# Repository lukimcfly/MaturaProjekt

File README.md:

# Maturaprojekt — Analoger Synthesizer

Physisches Produkt: analoger Synthesizer mit 3 Oszillatoren, Mixer, Amplifier
und Distortion. Dazu eine Fourier-Analyse von analogem und digitalem Ton sowie
die schriftlichen Abgabedokumente.

**Abgabetermin: 10. November 2026**
**Zwischenziel: physisches Produkt fertig bis zu den Herbstferien**

## Stand (22.09.2026)

**Alles bestellbereit.** Schaltplan, drei Platinen und Einkauf sind fertig; die
Warenkörbe bei Tayda, LCSC und Conrad sind gefüllt, JLCPCB braucht noch den Login.

| | |
|---|---|
| Gesamtschaltplan | ERC-sauber: 0 Fehler, 0 Warnungen |
| Oszillator-Platine (**3×** pro Gerät) | DRC-sauber, 0 offene Netze |
| Filter-Platine (**4×** pro Gerät) | DRC-sauber, 0 offene Netze |
| Hauptplatine (1×) | DRC-sauber, 0 offene Netze |
| Fertigungsdaten | vollständig in [`Platinen/Fertigung/`](Platinen/Fertigung/), inkl. Bestückung der SMD-Chips |
| Einkauf für 2 Geräte | **rund CHF 378** inkl. Platinen, Versand und MWST – [`Einkauf/BESTELLEN.md`](Einkauf/BESTELLEN.md) |

Nächster Schritt: bestellen, möglichst bis 24.09. (danach chinesische Feiertage).
Was sich am 22.09. geändert hat, steht im [Tagebuch vom 22.09.](diary/2026-09-22.md).

## Ordnerstruktur

| Ordner | Inhalt |
|---|---|
| [`diary/`](diary/README.md) | Arbeitstagebuch, eine Datei pro Arbeitstag |
| [`plan/`](plan/zeitplan-bis-herbstferien.md) | Zeitpläne |
| [`quellen/`](quellen/lernmaterial.md) | Lernmaterial, später Quellenverzeichnis |
| [`Bilder/`](Bilder/README.md) | Schaltpläne, Aufbaufotos, Messungen |
| [`Schul-Unterlagen/`](Schul-Unterlagen/README.md) | Vorgaben, Kriterien, Formulare von der Schule |
| [`Unsere-Materialien/`](Unsere-Materialien/README.md) | Logbuch und schriftlicher Kommentar zur Abgabe |
| [`SynthesizerFinal/`](SynthesizerFinal/README.md) | Gesamtschaltplan des Synthesizers (KiCad) |
| [`Platinen/`](Platinen/README.md) | Die drei Leiterplatten: Layout, Gerber, Stücklisten, Verdrahtung |
| [`Einkauf/`](Einkauf/BESTELLEN.md) | Einkaufsliste (Excel), Bestellanleitung, Sicherungskopien der Warenkörbe |
| [`Werkzeuge/`](Werkzeuge/README.md) | Die Skripte, mit denen Schaltplan und Platinen erzeugt wurden |
| `KicadCircuit/` | Ursprüngliche Einzelschaltpläne (Vorstufe, nur noch als Vergleich) |

## Arbeitsregel

Der Arbeitsprozess wird **immer direkt nach dem Arbeiten** dokumentiert.

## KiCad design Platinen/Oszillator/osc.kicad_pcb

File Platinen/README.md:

# Leiterplatten

Aus dem Gesamtschaltplan ([`../SynthesizerFinal/`](../SynthesizerFinal/README.md))
sind **drei** Leiterplatten abgeleitet. Nicht neun: die drei Oszillatoren sind
elektrisch identisch, die vier Filter ebenfalls — es gibt also drei Layouts, von
denen zwei mehrfach bestückt werden.

| Platine | Ordner | Stück | Grösse | Bauteile | Stand |
|---|---|---|---|---|---|
| Oszillator | [`Oszillator/`](Oszillator/) | **3×** | 108,1 × 108,1 mm | 57 | fertig geroutet, DRC sauber |
| Filter | [`Filter/`](Filter/) | **4×** | 80,1 × 68,1 mm | 22 | fertig geroutet, DRC sauber |
| Hauptplatine | [`Hauptplatine/`](Hauptplatine/) | 1× | 96,1 × 98,1 mm | 46 | fertig geroutet, DRC sauber |

Bei allen drei Platinen gilt: **kein DRC-Fehler, kein offenes Netz, Massefläche in
einem zusammenhängenden Stück.** Die Fertigungsdaten in `Fertigung/` sind
vollständig und gehören zu genau diesem Stand.

Filter und Hauptplatine bleiben unter **100 × 100 mm**. Das ist keine
willkürliche Grenze: die meisten günstigen Platinenhersteller haben genau dort
ihre Preisstufe.

Die **Oszillator-Platine ist grösser** — 108,1 × 108,1 mm. Sie trägt 57 Bauteile,
wo die Hauptplatine 46 auf ähnlicher Fläche trägt, und wurde vergrössert, weil
sich zwei Netze partout nicht routen liessen und Platzmangel als Ursache vermutet
wurde.

> **Diese Vermutung war falsch.** Die beiden Netze scheiterten an zwei *selbst
> gesetzten* Sperrflächen, nicht an der Fläche (siehe unten). Ob die Platine
> deshalb auch wieder unter 100 × 100 mm passt, ist **noch nicht nachgeprüft** —
> das steht als offener Punkt im [Tagebuch](../diary/2026-09-16.md). Solange das
> offen ist, gilt die 108-mm-Version: sie ist vollständig geroutet und geprüft.

> **Beim Bestellen beachten:** Mit 108 mm fällt diese eine Platine aus der
> 100-×-100-mm-Preisstufe, und sie wird **dreimal** gebraucht. Wer Geld sparen
> will, prüft vorher den offenen Punkt oben.

## Was wo liegt

| Ordner / Datei | Inhalt |
|---|---|
| `Oszillator/`, `Filter/`, `Hauptplatine/` | je ein vollständiges KiCad-Projekt (`.kicad_pro`, `.kicad_sch`, `.kicad_pcb`). Zum Ansehen das `.kicad_pro` öffnen |
| `Fertigung/*.zip` | die Dateien für den Platinenhersteller: Gerber, Bohrdaten, Bohrplan. So hochladen wie sie sind |
| `Stuecklisten/` | eine Stückliste pro Platine |
| [`VERDRAHTUNG.md`](VERDRAHTUNG.md) | **die wichtigste Datei beim Zusammenbau**: welches Kabel von wo nach wo, Draht für Draht |
| [`BEDIENFELD-ERGAENZUNGEN.md`](BEDIENFELD-ERGAENZUNGEN.md) | nachträglich dazugekommen: Oszillator ein/aus, Mixer-Fader, Lautsprecherklemmen statt eingebautem Lautsprecher, Modus-Taster, Arduino-Anschluss |
| `*-bestueckung.pdf` | Bestückungsplan zum Ausdrucken |

## Aufbau der Platinen

Zweilagig, Signale auf der Oberseite, **die ganze Unterseite ist Massefläche**.
Das ist bei Audio die entscheidende Entscheidung: der Rückstrom findet immer den
kürzesten Weg direkt unter seiner Leiterbahn, statt einen Umweg zu suchen und
dabei Störungen einzusammeln.

Leiterbahnen: 0,3 mm für Signale, 0,6 mm für die Versorgung.

### Eine bewusste Ausnahme auf der Oszillator-Platine

Beim Routen galt zusätzlich die selbst gesetzte Regel: **keine Leiterbahn auf der
Rückseite unter einem IC**. Ein Schlitz in der Massefläche zwingt den Rückstrom
zu einem Umweg, und ausgerechnet unter einem IC ist das am unangenehmsten.

Für **ein** Netz — `O1_AINV`, den Summierknoten von `U103` — ist diese Regel
aufgehoben. Ohne sie kam das Netz nicht durch, und zwar nachweislich: mit
Sperrfläche scheitert die Wegsuche auch nach **444 Sekunden**.

Was das kostet, ist nachgemessen und nicht geschätzt:

| | |
|---|---|
| Verlust an Massefläche | **73 mm² von 10 517 mm² = 0,69 %** |
| Massefläche danach | **ein** zusammenhängendes Stück, keine Inseln |
| Betroffenes IC | `U103` — **das IC, zu dem das Netz selbst führt** |

Der Schlitz liegt also unter dem Baustein, an dessen Pin die Leitung ohnehin
ankommt, nicht quer unter einem unbeteiligten IC. Und bei Audiofrequenzen
(≤ 20 kHz) fliesst der Rückstrom ohnehin breit verteilt; eng an der Leiterbahn
klebt er erst weit oberhalb von 1 MHz. Für eine Digitalplatine wäre das ein
Fehler, hier ist es vertretbar.

> Wer dieses Layout später überarbeitet: **den Schlitz nicht „aufräumen"**, ohne
> das Netz neu zu routen — sonst ist die Platine wieder unvollständig.

## Die Bedienelemente sitzen **nicht** auf den Platinen

Potis, Schalter und Buchsen kommen ins Bedienfeld und werden mit Kabeln an die
Platinen gesteckt (JST-XH, 2,5 mm). Das sind 153 Drähte, einer pro Lötfahne.
Alle stehen in [`VERDRAHTUNG.md`](VERDRAHTUNG.md).

> **Die Tabelle in `VERDRAHTUNG.md` genau befolgen.** Die Reihenfolge der Netze
> auf den Steckern ist nicht willkürlich, sondern so gewählt, dass die Leitungen
> den Stecker in derselben Reihenfolge verlassen wie die Bauteile stehen, die sie
> versorgen. Auf der Oszillator-Platine hat das **61 sich kreuzende Leitungspaare
> auf null** gebracht — und jede Kreuzung hätte den Router eine Durchkontaktierung
> oder einen Umweg gekostet, an der engsten Stelle der Platine. Wer die Drähte
> „logisch" umsortiert, macht das wieder kaputt.

## Wie das Layout entstanden ist

Die Platzierung ist **gerechnet, nicht gezeichnet**. Jedes Bauteil steht neben
dem IC-Pin, den es bedient, und seine Koordinaten kommen aus den echten
Pad-Positionen des Footprints. Der Schaltplan und das Layout können deshalb
nicht auseinanderlaufen.

Zwei Fehler hat das gefunden, die kein DRC je gemeldet hätte, weil es keine
Regelverletzungen sind:

- Der **Stützkondensator des LM386 stand 41 mm von seinem Versorgungspin** weg
  und das Zobel-Glied 32 bzw. 46 mm vom Ausgang. Ein LM386 mit so weit entfernter
  Abblockung und Bedämpfung ist ein zuverlässiges Rezept für einen Verstärker,
  der schwingt statt zu verstärken. Jetzt sind es 4,7 mm und 5,0 mm.
- Die **Klinkenbuchsen-Steckerleiste des Oszillators sass auf der linken
  Plattenkante**, obwohl alle drei Signale in die rechte Hälfte gehen — das hat
  `OSC1_OUT` über 98 mm quer über die Platine gezogen.

Die Skripte dazu liegen in [`../Werkzeuge/`](../Werkzeuge/README.md).

## Geprüft gegen die Fertigungsgrenzen von JLCPCB (21.09.2026)

Hersteller: **JLCPCB** (https://jlcpcb.com). Alle drei Platinen wurden mit
[`../Werkzeuge/jlccheck.py`](../Werkzeuge/jlccheck.py) direkt aus den Platinendateien
vermessen und mit der Tabelle unter https://jlcpcb.com/capabilities/pcb-capabilities
verglichen – bei widersprüchlichen Angaben dort jeweils mit dem strengeren Wert.

| Prüfpunkt | JLCPCB min. | Unsere Platinen |
|---|---|---|
| Leiterbahnbreite | 0,127 mm | 0,3 mm |
| Via-Bohrung | 0,3 mm | 0,4 mm |
| Via-Restring | 0,15 mm | 0,2 mm |
| Restring bedrahteter Pads | 0,25 mm (empfohlen) | 0,35 mm |
| Befestigungslöcher (NPTH) | 0,5 mm | 3,2 mm |
| Loch-zu-Loch | 0,45 mm | ≥ 0,85 mm |
| Kupfer zur Platinenkante | 0,2 mm | 0,3 mm |
| Bestückungsdruck: Schrifthöhe / Strichstärke | 1,0 / 0,15 mm | 1,0 / 0,15 mm |
| Bestückungsdruck: Linien | 0,15 mm | 0,15 mm |

**Eine Änderung war nötig:** Die Bauteil-Umrisse aus der KiCad-Standardbibliothek
sind mit 0,12 mm gezeichnet – dünner als die 0,15 mm, die JLCPCB zuverlässig druckt.
[`silkwiden.py`](../Werkzeuge/silkwiden.py) hat alle 2 468 solchen Linien auf 0,15 mm
verbreitert. Nur die Strichstärke hat sich geändert; an Kupfer, Bohrungen und
Bauteilpositionen nichts. Danach erneut geprüft: DRC fehlerfrei, kein offenes Netz,
Masseflächen auf den Quadratmillimeter gleich wie vorher. Der Stand davor liegt im
Archiv (`archiv/<platine>/rev4-pre-jlc/`).

**Einstellungen beim Bestellen** (alles andere auf Standard lassen): Layers 2 ·
PCB Thickness 1,6 mm · Surface Finish **HASL (with lead)** – das bleifreie HASL kostet
1,60 USD pro Platinensorte mehr und bringt beim Handlöten nichts · Stückzahl siehe
unten. Die Schritt-für-Schritt-Anleitung steht in [`../Einkauf/BESTELLEN.md`](../Einkauf/BESTELLEN.md).

## Bestückung: gemischt (JLCPCB + von Hand)

Entschieden am 21.09.2026: **JLCPCB lötet nur die SMD-Chips** – drei auf der
Oszillator-Platine, einer auf der Filter-Platine –, alles andere wird von Hand
bestückt. Diese winzigen Chips sind das Einzige, was sich von Hand schwer löten lässt; alles Übrige ist bedrahtet,
lässt sich leicht tauschen, und die Potis sitzen ohnehin im Bedienfeld.

| Bauteil | Typ | Gehäuse | LCSC-Nr. |
|---|---|---|---|
| U102 | SN74LVC2G17DBVR | SOT-23-6 | C10429 |
| U103 | **TL074CDR** | SOIC-14 | **C12594** |
| U104 | OPA1662AIDR | SOIC-8 | C882794 |
| U401 (Filter) | **TL074CDR** | SOIC-14 | **C12594** |

**Geändert am 22.09.2026: TL074CDR statt OPA4196.** Beide sind Vierfach-Op-Amps mit
derselben Anschlussbelegung im selben Gehäuse; am Layout ändert sich nichts. Der
OPA4196 kostet 3,62 USD, der TL074CDR 0,29 USD – und weil JLCPCB bei 10 Platinen
alle 10 bestücken muss, wären es 20 Stück gewesen. Geprüft:

* Netzliste vorher/nachher: **genau 7 Wertänderungen** (U103, U203, U303, U401–U701),
  keine Netz- und keine Footprint-Änderung; ERC und DRC fehlerfrei.
* Filter (U401): Simulation mit beiden Op-Amp-Modellen über den ganzen Cutoff- und
  Resonanzbereich – Unterschied **unter 0,1 dB**. Der TL074 ist hier sogar schneller
  (3 MHz / 13 V/µs gegenüber 2,5 MHz / 5,5 V/µs).
* Oszillator (U103): Puffer der Sägezahn-Kapazität (Eingang 0…3,4 V, Eingangsstrom
  des TL074 30 pA gegen ≥ 1,6 µA Ladestrom – vernachlässigbar), Drive-,
  Make-up- und Sägezahn-Ausgangsstufe mit Signalen weit unter ±10 V. Die
  Tonhöhe hängt nicht vom Op-Amp ab, sondern von den Schmitt-Trigger-Schwellen.
* Der Wert steht nur auf der Fab-Lage, nicht im Bestückungsdruck – die Gerber-Dateien
  sind dadurch nicht verändert.

**Neu im Gerber-Paket:** die **Lotpasten-Lage** (`F_Paste`) bei Oszillator und
Filter. Ohne sie kann JLCPCB keine Schablone für die SMD-Chips schneiden; die
Hauptplatine hat keine SMD-Teile und braucht keine. Die übrigen Lagen sind
byte-gleich bis auf den Zeitstempel.

Dateien für die Bestellung in `Fertigung/`: je eine `…-BOM-jlcpcb.csv` und
`…-CPL-jlcpcb.csv` für Oszillator und Filter. Bei diesen beiden Platinen
**PCB Assembly** einschalten (Economic, Top Side) und die passenden zwei Dateien
hochladen.

**Stückzahl:** JLCPCB lässt bei 10 Platinen nur „alle 10 bestücken" zu (eine
Teilbestückung gibt es nur bei 5 Stück: 2 von 5). Für 2 Geräte also: Oszillator
**10 Stück, alle bestückt** (6 gebraucht), Filter **10 Stück, alle bestückt**
(8 gebraucht), Hauptplatine **5 Stück, ohne Bestückung** (2 gebraucht). Die
überzähligen bestückten Platinen sind Reserve – die Mehrkosten sind mit dem TL074
nur noch rund 6 USD.

> **In der Vorschau von JLCPCB die Ausrichtung prüfen:** Der Punkt für Pin 1 jedes
> Chips muss auf der Markierung im Bestückungsdruck liegen. JLCPCB zählt die
> Drehung bei manchen Gehäusen anders als KiCad; falls ein Chip verdreht angezeigt
> wird, dort drehen, bevor bestellt wird.

Die Hauptplatine hat keine SMD-Teile – dort **keine** Bestückung wählen.

## Vor dem Bestellen

- [ ] Die Gerber in einem Viewer ansehen (z. B. der kostenlose Online-Viewer des
      Herstellers) — nicht blind hochladen.
- [ ] Stückzahl für 2 Geräte: Oszillator 10, Filter 10, Hauptplatine 5 (siehe oben).
- [ ] Die Oszillator-Platine (108 mm) fällt aus der 100-mm-Preisstufe: 15,30 statt
      5,00 USD für 10 Stück. Sie zu verkleinern hiesse, die dichteste Platine neu zu
      routen – für rund 10 USD bewusst nicht gemacht.

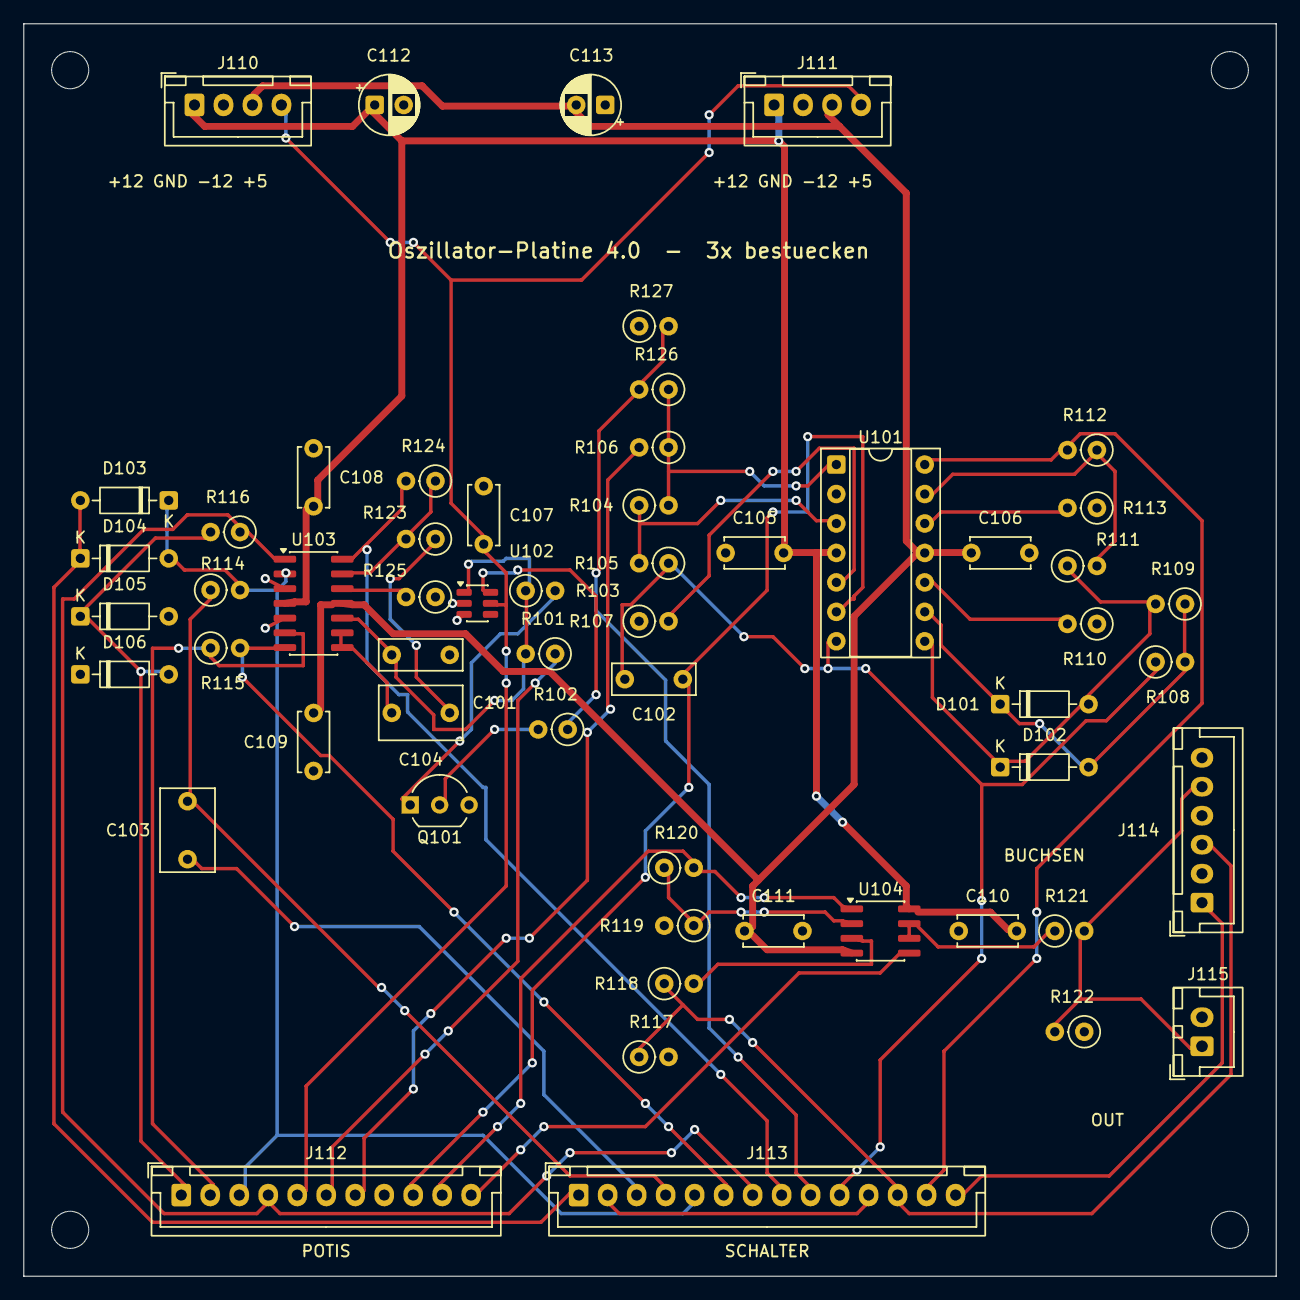
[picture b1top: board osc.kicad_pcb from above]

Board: 2 copper layers, 108.0 x 108.0 mm, 61 parts (0 on the bottom side), 44 nets.

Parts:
C101: 56nF; C_Rect_L7.0mm_W2.5mm_P5.00mm
C102: 15nF; C_Rect_L7.0mm_W2.5mm_P5.00mm
C103, C104: 1uF; C_Rect_L7.0mm_W4.5mm_P5.00mm
C105, C106, C107, C108, C109, C110, C111: 100nF; C_Disc_D5.0mm_W2.5mm_P5.00mm
C112, C113: 10uF/25V; CP_Radial_D5.0mm_P2.50mm
D101, D102, D103, D104, D105, D106: 1N4148; D_DO-35_SOD27_P7.62mm_Horizontal
H1, H2, H3, H4: MountingHole_3.2mm_M3
J110: Versorgung ein; JST_XH_B4B-XH-A_1x04_P2.50mm_Vertical
J111: Versorgung weiter; JST_XH_B4B-XH-A_1x04_P2.50mm_Vertical
J112: Panel Potis; JST_XH_B11B-XH-A_1x11_P2.50mm_Vertical
J113: Panel Schalter; JST_XH_B14B-XH-A_1x14_P2.50mm_Vertical
J114: Panel Buchsen; JST_XH_B6B-XH-A_1x06_P2.50mm_Vertical
J115: Audio aus -> Mixer; JST_XH_B2B-XH-A_1x02_P2.50mm_Vertical
Q101: BC547; TO-92_Inline_Wide
R101, R106, R107, R109, R110, R111, R113, R114, R118, R119, R120, R123, R125, R127: 10k; R_Axial_DIN0207_L6.3mm_D2.5mm_P2.54mm_Vertical
R102: 1k; R_Axial_DIN0207_L6.3mm_D2.5mm_P2.54mm_Vertical
R103: 220; R_Axial_DIN0207_L6.3mm_D2.5mm_P2.54mm_Vertical
R104, R108: 47k; R_Axial_DIN0207_L6.3mm_D2.5mm_P2.54mm_Vertical
R105: 16k; R_Axial_DIN0207_L6.3mm_D2.5mm_P2.54mm_Vertical
R112: 82k; R_Axial_DIN0207_L6.3mm_D2.5mm_P2.54mm_Vertical
R115: 330k; R_Axial_DIN0207_L6.3mm_D2.5mm_P2.54mm_Vertical
R116: 2.2k; R_Axial_DIN0207_L6.3mm_D2.5mm_P2.54mm_Vertical
R117, R122: 100k; R_Axial_DIN0207_L6.3mm_D2.5mm_P2.54mm_Vertical
R121: 100; R_Axial_DIN0207_L6.3mm_D2.5mm_P2.54mm_Vertical
R124: 56k; R_Axial_DIN0207_L6.3mm_D2.5mm_P2.54mm_Vertical
R126: 20k; R_Axial_DIN0207_L6.3mm_D2.5mm_P2.54mm_Vertical
U101: TL074; DIP-14_W7.62mm_Socket
U102: 74LVC2G17; SOT-23-6
U103: TL074CDR; SOIC-14_3.9x8.7mm_P1.27mm
U104: OPA1662; SOIC-8_3.9x4.9mm_P1.27mm

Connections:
+5V: C107.1, J110.4, J111.4, J112.5, U102.5
+12V: C105.1, C108.1, C110.1, C112.1, J110.1, J111.1, U101.4, U103.4, U104.8
-12V: C106.2, C109.2, C111.2, C113.2, J110.3, J111.3, U101.11, U103.11, U104.4
/O1_AINV: D103.1, D104.2, J112.3, J113.5, R114.2, U103.2
/O1_CLIP: D105.1, D106.2, J112.1, R116.2
/O1_DRIVE: J112.4, J113.7, R116.1, U103.1
/O1_FGF_A: J112.7, R106.2
/O1_FGF_B: C102.1, J112.9, U101.6
/O1_LVL_A: J112.10, R120.2, U104.1
/O1_LVL_W: J112.11, U104.5
/O1_MKUP: J113.6, R115.2, U103.7
/O1_MKUP_A: J112.2, R115.1, U103.6
/O1_PITCH: J112.6, R101.1
/O1_SEND: J113.14, J114.1
/O1_SOFT: D103.2, D104.1, J113.1
/O1_WSEL: C103.1, J113.3
/OSC1_DIST: J113.2, J113.11
/OSC1_OUT: J114.5, J115.1, R121.2, R122.2
/OSC1_SAW: J113.8, R124.2, U103.14
/OSC1_SIG: J113.12, J114.3, R117.1, R118.1
/OSC1_SINE: J113.13, R112.2, U101.14
/OSC1_SQ: J113.9, R126.2, R127.2
/OSC1_TRI: C102.2, J113.10, R105.1, R108.1, U101.7
/OSC1_WAVE: C103.2, J113.4, R114.1
GNDREF: C101.2, C105.2, C106.1, C107.2, C108.2, C109.1, C110.2, C111.1, C112.2, C113.1, D105.2, D106.1, J110.2, J111.2, J112.8, J114.2, J114.4, J114.6, J115.2, Q101.3, R107.1, R110.1, R113.1, R117.2, R119.2, R122.1, R125.1, R127.1, U101.2, U102.2, U102.3, U103.3, U103.5
unnamed: C104.2, R123.1
unnamed: D101.2, D102.1, R109.2, R111.1, U101.8
unnamed: D101.1, D102.2, R108.2, R109.1, U101.9
unnamed: Q101.2, R102.2
unnamed: Q101.1, R103.2
unnamed: R102.1, U102.6
unnamed: R104.2, R106.1, R126.1, U101.1
unnamed: R104.1, R105.2, U101.3
unnamed: R107.2, U101.5
unnamed: R110.2, U101.10
unnamed: R113.2, U101.12
unnamed: R111.2, R112.1, U101.13
unnamed: C101.1, R101.2, R103.1, U102.1, U103.10
unnamed: C104.1, U103.8, U103.9
unnamed: R125.2, U103.12
unnamed: R123.2, R124.1, U103.13
unnamed: R118.2, U104.3
unnamed: R119.1, R120.1, U104.2
unnamed: R121.1, U104.6, U104.7

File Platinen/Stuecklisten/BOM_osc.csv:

"Reference","Value","Footprint"
"C101","56nF","Capacitor_THT:C_Rect_L7.0mm_W2.5mm_P5.00mm"
"C102","15nF","Capacitor_THT:C_Rect_L7.0mm_W2.5mm_P5.00mm"
"C103,C104","1uF","Capacitor_THT:C_Rect_L7.0mm_W4.5mm_P5.00mm"
"C105-C111","100nF","Capacitor_THT:C_Disc_D5.0mm_W2.5mm_P5.00mm"
"C112,C113","10uF/25V","Capacitor_THT:CP_Radial_D5.0mm_P2.50mm"
"D101-D106","1N4148","Diode_THT:D_DO-35_SOD27_P7.62mm_Horizontal"
"J101","Filter-Send",""
"J102","Filter-Return",""
"J103","Ausgang",""
"J110","Versorgung ein","Connector_JST:JST_XH_B4B-XH-A_1x04_P2.50mm_Vertical"
"J111","Versorgung weiter","Connector_JST:JST_XH_B4B-XH-A_1x04_P2.50mm_Vertical"
"J112","Panel Potis","Connector_JST:JST_XH_B11B-XH-A_1x11_P2.50mm_Vertical"
"J113","Panel Schalter","Connector_JST:JST_XH_B14B-XH-A_1x14_P2.50mm_Vertical"
"J114","Panel Buchsen","Connector_JST:JST_XH_B6B-XH-A_1x06_P2.50mm_Vertical"
"J115","Audio aus -> Mixer","Connector_JST:JST_XH_B2B-XH-A_1x02_P2.50mm_Vertical"
"Q101","BC547","Package_TO_SOT_THT:TO-92_Inline_Wide"
"R101,R106,R107,R109-R111,R113,R114,R118-R120,R123,R125,R127","10k","Resistor_THT:R_Axial_DIN0207_L6.3mm_D2.5mm_P2.54mm_Vertical"
"R102","1k","Resistor_THT:R_Axial_DIN0207_L6.3mm_D2.5mm_P2.54mm_Vertical"
"R103","220","Resistor_THT:R_Axial_DIN0207_L6.3mm_D2.5mm_P2.54mm_Vertical"
"R104,R108","47k","Resistor_THT:R_Axial_DIN0207_L6.3mm_D2.5mm_P2.54mm_Vertical"
"R105","16k","Resistor_THT:R_Axial_DIN0207_L6.3mm_D2.5mm_P2.54mm_Vertical"
"R112","82k","Resistor_THT:R_Axial_DIN0207_L6.3mm_D2.5mm_P2.54mm_Vertical"
"R115","330k","Resistor_THT:R_Axial_DIN0207_L6.3mm_D2.5mm_P2.54mm_Vertical"
"R116","2.2k","Resistor_THT:R_Axial_DIN0207_L6.3mm_D2.5mm_P2.54mm_Vertical"
"R117,R122","100k","Resistor_THT:R_Axial_DIN0207_L6.3mm_D2.5mm_P2.54mm_Vertical"
"R121","100","Resistor_THT:R_Axial_DIN0207_L6.3mm_D2.5mm_P2.54mm_Vertical"
"R124","56k","Resistor_THT:R_Axial_DIN0207_L6.3mm_D2.5mm_P2.54mm_Vertical"
"R126","20k","Resistor_THT:R_Axial_DIN0207_L6.3mm_D2.5mm_P2.54mm_Vertical"
"RV101,RV102","1M lin",""
"RV103","100k lin",""
"RV104","100k log",""
"RV105","10k log",""
"SW101","Wellenform",""
"SW102","weich/hart",""
"SW103","Distortion ein/aus",""
"SW104","Solo-Filter ein/aus",""
"U101","TL074","Package_DIP:DIP-14_W7.62mm_Socket"
"U102","74LVC2G17","Package_TO_SOT_SMD:SOT-23-6"
"U103","TL074CDR","Package_SO:SOIC-14_3.9x8.7mm_P1.27mm"
"U104","OPA1662","Package_SO:SOIC-8_3.9x4.9mm_P1.27mm"

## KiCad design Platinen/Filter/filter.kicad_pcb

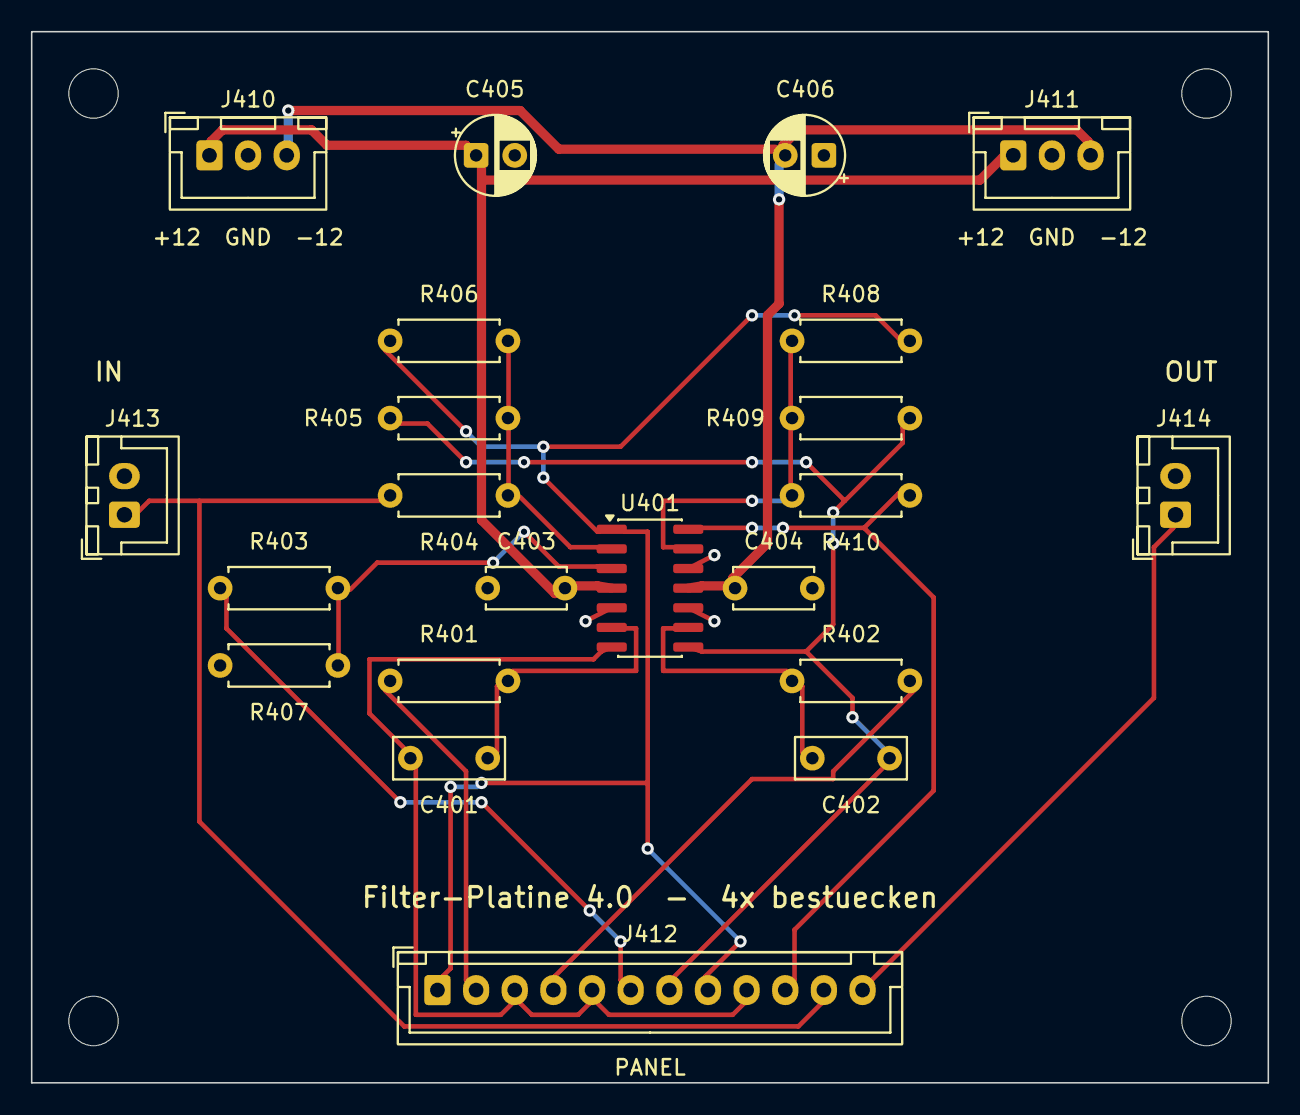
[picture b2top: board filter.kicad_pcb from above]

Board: 2 copper layers, 80.0 x 68.0 mm, 26 parts (0 on the bottom side), 17 nets.

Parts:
C401, C402: 15nF; C_Rect_L7.0mm_W2.5mm_P5.00mm
C403, C404: 100nF; C_Disc_D5.0mm_W2.5mm_P5.00mm
C405, C406: 10uF/25V; CP_Radial_D5.0mm_P2.50mm
H1, H2, H3, H4: MountingHole_3.2mm_M3
J410: Versorgung ein; JST_XH_B3B-XH-A_1x03_P2.50mm_Vertical
J411: Versorgung weiter; JST_XH_B3B-XH-A_1x03_P2.50mm_Vertical
J412: Panel Poti + Wahlschalter; JST_XH_B12B-XH-A_1x12_P2.50mm_Vertical
J413: Audio ein; JST_XH_B2B-XH-A_1x02_P2.50mm_Vertical
J414: Audio aus; JST_XH_B2B-XH-A_1x02_P2.50mm_Vertical
R401, R402: 1k; R_Axial_DIN0207_L6.3mm_D2.5mm_P7.62mm_Horizontal
R403, R407: 6.8k; R_Axial_DIN0207_L6.3mm_D2.5mm_P7.62mm_Horizontal
R404, R405, R406, R408, R409, R410: 10k; R_Axial_DIN0207_L6.3mm_D2.5mm_P7.62mm_Horizontal
U401: TL074CDR; SOIC-14_3.9x8.7mm_P1.27mm

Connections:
+12V: C403.1, C405.1, J410.1, J411.1, U401.4
-12V: C404.2, C406.2, J410.3, J411.3, U401.11
/F4_BP: C401.2, J412.3, J412.5, J412.9, U401.7
/F4_HP: J412.1, J412.8, R406.1, R408.1, U401.1
/F4_LP: C402.2, J412.7, R405.1, R409.1, U401.8
/F4_NOTCH: J412.10, R410.2, U401.14
/F4_RESW: J412.6, R403.1
/F4_T1W: J412.2, R401.1
/F4_T2W: J412.4, R402.1
/FILT_A_OUT: J412.12, J414.1
/MIX_OUT: J412.11, J413.1, R404.1
GNDREF: C403.2, C404.1, C405.2, C406.1, J410.2, J411.2, J413.2, J414.2, R407.1, U401.5, U401.10, U401.12
unnamed: R403.2, R407.2, U401.3
unnamed: R404.2, R405.2, R406.2, U401.2
unnamed: C401.1, R401.2, U401.6
unnamed: C402.1, R402.2, U401.9
unnamed: R408.2, R409.2, R410.1, U401.13

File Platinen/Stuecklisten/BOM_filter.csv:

"Reference","Value","Footprint"
"C401,C402","15nF","Capacitor_THT:C_Rect_L7.0mm_W2.5mm_P5.00mm"
"C403,C404","100nF","Capacitor_THT:C_Disc_D5.0mm_W2.5mm_P5.00mm"
"C405,C406","10uF/25V","Capacitor_THT:CP_Radial_D5.0mm_P2.50mm"
"J410","Versorgung ein","Connector_JST:JST_XH_B3B-XH-A_1x03_P2.50mm_Vertical"
"J411","Versorgung weiter","Connector_JST:JST_XH_B3B-XH-A_1x03_P2.50mm_Vertical"
"J412","Panel Poti + Wahlschalter","Connector_JST:JST_XH_B12B-XH-A_1x12_P2.50mm_Vertical"
"J413","Audio ein","Connector_JST:JST_XH_B2B-XH-A_1x02_P2.50mm_Vertical"
"J414","Audio aus","Connector_JST:JST_XH_B2B-XH-A_1x02_P2.50mm_Vertical"
"R401,R402","1k","Resistor_THT:R_Axial_DIN0207_L6.3mm_D2.5mm_P7.62mm_Horizontal"
"R403,R407","6.8k","Resistor_THT:R_Axial_DIN0207_L6.3mm_D2.5mm_P7.62mm_Horizontal"
"R404-R406,R408-R410","10k","Resistor_THT:R_Axial_DIN0207_L6.3mm_D2.5mm_P7.62mm_Horizontal"
"RV401,RV402","100k lin",""
"RV403","47k lin",""
"SW401","Filterwahl",""
"U401","TL074CDR","Package_SO:SOIC-14_3.9x8.7mm_P1.27mm"

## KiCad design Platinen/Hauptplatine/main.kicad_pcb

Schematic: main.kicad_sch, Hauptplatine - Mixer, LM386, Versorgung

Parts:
C801, C802, C803: 1uF; C_Rect_L7.0mm_W4.5mm_P5.00mm
C804, C903: 10uF/16V; CP_Radial_D5.0mm_P2.50mm
C805: 470uF/16V; CP_Radial_D10.0mm_P5.00mm
C806: 47uF/25V; CP_Radial_D6.3mm_P2.50mm
C901: 10uF/25V bipolar; CP_Radial_D5.0mm_P2.50mm
C904: 470uF/25V; CP_Radial_D10.0mm_P5.00mm
C905: 47nF; C_Rect_L7.0mm_W2.5mm_P5.00mm
C906, C931, C932: 100uF/25V; CP_Radial_D6.3mm_P2.50mm
C907, C921, C922, C942: 100nF; C_Disc_D5.0mm_W2.5mm_P5.00mm
C941: 330nF; C_Rect_L7.0mm_W2.5mm_P5.00mm
D907, D908: 1N5819; D_DO-41_SOD81_P10.16mm_Horizontal
F901, F902: T500mA; Fuseholder_Clip-5x20mm_Littelfuse_111_Inline_P20.00x5.00mm_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
J810: Versorgung -> Oszillatoren; JST_XH_B4B-XH-A_1x04_P2.50mm_Vertical
J811: Versorgung -> Filter; JST_XH_B3B-XH-A_1x03_P2.50mm_Vertical
J812: Panel Potis; JST_XH_B12B-XH-A_1x12_P2.50mm_Vertical
J813: OSC 1 ein; JST_XH_B2B-XH-A_1x02_P2.50mm_Vertical
J814: OSC 2 ein; JST_XH_B2B-XH-A_1x02_P2.50mm_Vertical
J815: OSC 3 ein; JST_XH_B2B-XH-A_1x02_P2.50mm_Vertical
J816: -> Filter A; JST_XH_B2B-XH-A_1x02_P2.50mm_Vertical
J817: Filter B ->; JST_XH_B2B-XH-A_1x02_P2.50mm_Vertical
J904: Lautsprecher 8R; JST_XH_B2B-XH-A_1x02_P2.50mm_Vertical
J990: Netzteil +/-12V; JST_XH_B3B-XH-A_1x03_P2.50mm_Vertical
Q801: BC547; TO-92_Inline_Wide
R801, R802, R803, R809: 100k; R_Axial_DIN0207_L6.3mm_D2.5mm_P7.62mm_Horizontal
R804: 47k; R_Axial_DIN0207_L6.3mm_D2.5mm_P7.62mm_Horizontal
R805: 10k; R_Axial_DIN0207_L6.3mm_D2.5mm_P7.62mm_Horizontal
R806: 470; R_Axial_DIN0207_L6.3mm_D2.5mm_P7.62mm_Horizontal
R807: 100; R_Axial_DIN0207_L6.3mm_D2.5mm_P7.62mm_Horizontal
R808: 1; R_Axial_DIN0207_L6.3mm_D2.5mm_P7.62mm_Horizontal
R901: 10; R_Axial_DIN0207_L6.3mm_D2.5mm_P7.62mm_Horizontal
R902: 68k; R_Axial_DIN0207_L6.3mm_D2.5mm_P7.62mm_Horizontal
RV801, RV802, RV803, RV901: 10k log
U901: LM386; DIP-8_W7.62mm_Socket
U990: 78L05; TO-92_Inline_Wide

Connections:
+5V: C942.1, J810.4, U990.1 (VO)
+12V: C906.1, C907.1, C921.1, C931.1, C941.1, D907.1 (K), J810.1, J811.1, R804.1, R806.1, U901.6 (V+), U990.3 (VI)
-12V: C922.2, C932.2, D908.2 (A), J810.3, J811.3
/FILT_B_OUT: C901.1, J817.1
/MIX_OUT: C806.2, J816.1, R809.1
/M_LVL1_A: C801.2, J812.1, RV801.1
/M_LVL1_W: J812.2, R801.1, RV801.2
/M_LVL2_A: C802.2, J812.4, RV802.1
/M_LVL2_W: J812.5, R802.1, RV802.2
/M_LVL3_A: C803.2, J812.7, RV803.1
/M_LVL3_W: J812.8, R803.1, RV803.2
/M_VOL_A: J812.10, R902.2, RV901.1
/M_VOL_W: J812.11, RV901.2, U901.3 (+)
/OSC1_OUT: C801.1, J813.1
/OSC2_OUT: C802.1, J814.1
/OSC3_OUT: C803.1, J815.1
/VIN_N: F902.1, J990.3
/VIN_P: F901.1, J990.1
GNDREF: C805.2, C903.2, C905.2, C906.2, C907.2, C921.2, C922.1, C931.2, C932.1, C941.2, C942.2, J810.2, J811.2, J812.3, J812.6, J812.9, J812.12, J813.2, J814.2, J815.2, J816.2, J817.2, J904.2, J990.2, R805.2, R808.2, R809.2, RV801.3, RV802.3, RV803.3, RV901.3, U901.2 (-), U901.4 (GND), U990.2 (GND)
unnamed: C804.2, R801.2, R802.2, R803.2
unnamed: C805.1, R807.2, R808.1
unnamed: C901.2, R902.1
unnamed: C904.1, R901.1, U901.5
unnamed: C905.1, R901.2
unnamed: D907.2 (A), F901.2
unnamed: D908.1 (K), F902.2
unnamed: C904.2, J904.1
unnamed: C804.1, Q801.2 (B), R804.2, R805.1
unnamed: C806.1, Q801.1 (C), R806.2
unnamed: Q801.3 (E), R807.1
unnamed: C903.1, U901.7 (BYPASS)

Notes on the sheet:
STROMVERSORGUNG DER OPERATIONSVERSTAERKER
VERSORGUNG, ABBLOCKUNG UND +5 V
Mixer / Endstufe
Uebernommen aus der Falstad-Simulation. R809 (1k) = Lastwiderstand aus der Simulation.
SIGNALWEG (durchgehend verdrahtet): Oszillator 1/2/3 -> Mixer -> Filter A -> Filter B -> LM386 -> Lautsprecher Die Solo-Filter C und D werden per Klinkenkabel in den Filter-Port eines Oszillators eingeschleift.
MIXER - 3-Kanal Summierer + BC547 Verstaerkerstufe
VERPOLUNGS- UND UEBERSTROMSCHUTZ
F901/F902 begrenzen den Strom bei einem Kurzschluss. D907/D908 (Schottky) sperren, wenn der Netzstecker verpolt ist: +12 V und -12 V koennen dann nicht vertauscht an die ICs gelangen. Spannungsverlust ca. 0,3 V pro Schiene.
ENDVERSTAERKER - LM386 + Lautsprecher

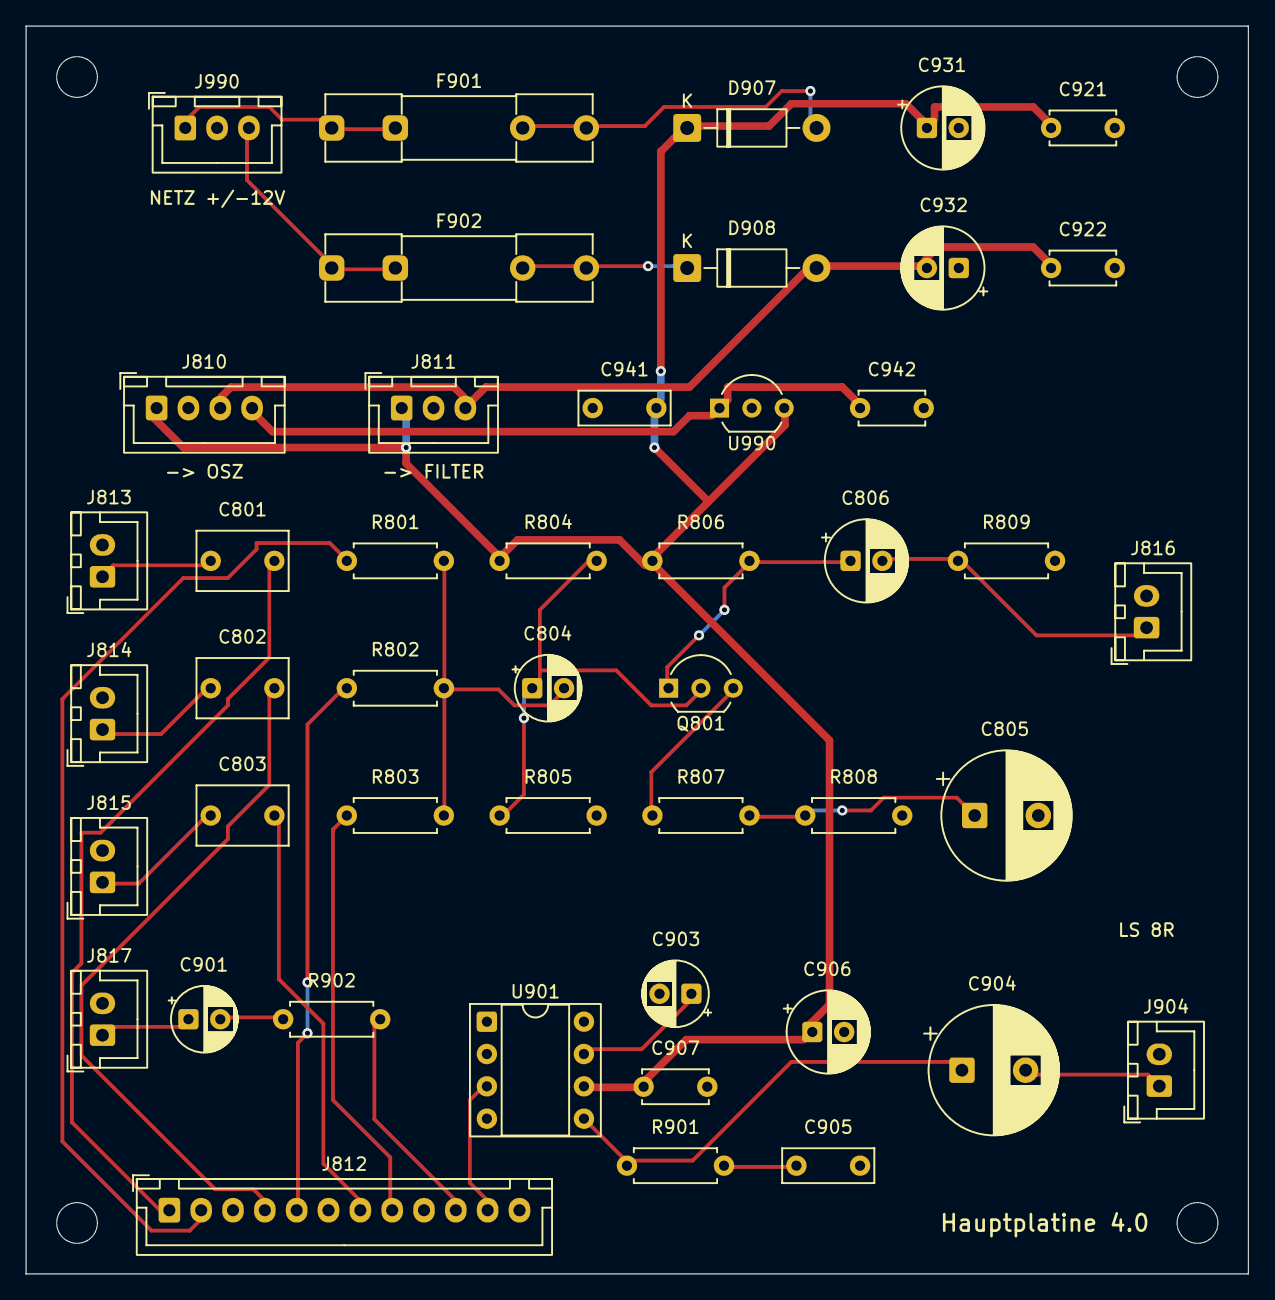
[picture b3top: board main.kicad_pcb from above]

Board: 2 copper layers, 96.0 x 98.0 mm, 50 parts (0 on the bottom side), 31 nets.

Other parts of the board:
H1, H2, H3, H4: MountingHole_3.2mm_M3

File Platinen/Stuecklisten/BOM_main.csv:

"Reference","Value","Footprint"
"C801-C803","1uF","Capacitor_THT:C_Rect_L7.0mm_W4.5mm_P5.00mm"
"C804,C903","10uF/16V","Capacitor_THT:CP_Radial_D5.0mm_P2.50mm"
"C805","470uF/16V","Capacitor_THT:CP_Radial_D10.0mm_P5.00mm"
"C806","47uF/25V","Capacitor_THT:CP_Radial_D6.3mm_P2.50mm"
"C901","10uF/25V bipolar","Capacitor_THT:CP_Radial_D5.0mm_P2.50mm"
"C904","470uF/25V","Capacitor_THT:CP_Radial_D10.0mm_P5.00mm"
"C905","47nF","Capacitor_THT:C_Rect_L7.0mm_W2.5mm_P5.00mm"
"C906,C931,C932","100uF/25V","Capacitor_THT:CP_Radial_D6.3mm_P2.50mm"
"C907,C921,C922,C942","100nF","Capacitor_THT:C_Disc_D5.0mm_W2.5mm_P5.00mm"
"C941","330nF","Capacitor_THT:C_Rect_L7.0mm_W2.5mm_P5.00mm"
"D907,D908","1N5819","Diode_THT:D_DO-41_SOD81_P10.16mm_Horizontal"
"F901,F902","T500mA","Fuse:Fuseholder_Clip-5x20mm_Littelfuse_111_Inline_P20.00x5.00mm_D1.05mm_Horizontal"
"J810","Versorgung -> Oszillatoren","Connector_JST:JST_XH_B4B-XH-A_1x04_P2.50mm_Vertical"
"J811","Versorgung -> Filter","Connector_JST:JST_XH_B3B-XH-A_1x03_P2.50mm_Vertical"
"J812","Panel Potis","Connector_JST:JST_XH_B12B-XH-A_1x12_P2.50mm_Vertical"
"J813","OSC 1 ein","Connector_JST:JST_XH_B2B-XH-A_1x02_P2.50mm_Vertical"
"J814","OSC 2 ein","Connector_JST:JST_XH_B2B-XH-A_1x02_P2.50mm_Vertical"
"J815","OSC 3 ein","Connector_JST:JST_XH_B2B-XH-A_1x02_P2.50mm_Vertical"
"J816","-> Filter A","Connector_JST:JST_XH_B2B-XH-A_1x02_P2.50mm_Vertical"
"J817","Filter B ->","Connector_JST:JST_XH_B2B-XH-A_1x02_P2.50mm_Vertical"
"J904","Lautsprecher 8R","Connector_JST:JST_XH_B2B-XH-A_1x02_P2.50mm_Vertical"
"J990","Netzteil +/-12V","Connector_JST:JST_XH_B3B-XH-A_1x03_P2.50mm_Vertical"
"Q801","BC547","Package_TO_SOT_THT:TO-92_Inline_Wide"
"R801-R803,R809","100k","Resistor_THT:R_Axial_DIN0207_L6.3mm_D2.5mm_P7.62mm_Horizontal"
"R804","47k","Resistor_THT:R_Axial_DIN0207_L6.3mm_D2.5mm_P7.62mm_Horizontal"
"R805","10k","Resistor_THT:R_Axial_DIN0207_L6.3mm_D2.5mm_P7.62mm_Horizontal"
"R806","470","Resistor_THT:R_Axial_DIN0207_L6.3mm_D2.5mm_P7.62mm_Horizontal"
"R807","100","Resistor_THT:R_Axial_DIN0207_L6.3mm_D2.5mm_P7.62mm_Horizontal"
"R808","1","Resistor_THT:R_Axial_DIN0207_L6.3mm_D2.5mm_P7.62mm_Horizontal"
"R901","10","Resistor_THT:R_Axial_DIN0207_L6.3mm_D2.5mm_P7.62mm_Horizontal"
"R902","68k","Resistor_THT:R_Axial_DIN0207_L6.3mm_D2.5mm_P7.62mm_Horizontal"
"RV801-RV803,RV901","10k log",""
"U901","LM386","Package_DIP:DIP-8_W7.62mm_Socket"
"U990","78L05","Package_TO_SOT_THT:TO-92_Inline_Wide"
